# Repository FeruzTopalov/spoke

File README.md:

# **SPOKE*** - _Stay close!_ 
_*Like a spoke in a wheel_

<p align="center">
🔓 Open-source<br>
🛠️ Open-hardware<br>
🛰️ GPS-based<br>
📡 LoRa-enabled<br>
🔋 Off-grid<br>
✨ Feature-rich<br>
🧭 Local Relative Navigation System<br>
<br>
or<br>
<br>
📍 just a LoRa GPS tracker for group 😉<br>
</p>

---

## 📋 Table of Contents

- [About](#about)
- [Use Cases](#use-cases)
- [Key Features](#key-features)
- [Hardware](#hardware)
- [Technology & How It Works](#technology--how-it-works)
- [Navigation Algorithms](#navigation-algorithms)
- [Getting Started](#getting-started)
- [Configuration](#configuration)
- [Frequency Bands](#frequency-bands)
- [Community](#community)
- [Contributing](#contributing)
- [Support the Project](#support-the-project)

---

## About

**Spoke** is a GPS tracker for a group of up to 5 members. It enables **real-time positional data sharing** in a group, providing **Distance** and **Azimuth** information in a **radar-like interface** where a 360-degree azimuth circle shows your direction as a **spoke** and azimuth to target as a **notch**. 

Besides navigation function, Spoke has **extra safety features** like: 
- **Alarm distress signal** - with a dedicated red button to easily call group members for help
- **Timeout alert** - with configurable timeout in seconds
- **Radial geo-fence alert** - with configurable distance in meters

---

## Use Cases

Spoke's open-source nature and flexible hardware make it adaptable to numerous scenarios:

- 🥾 **Hiking & Trekking** - Keep your group together on trails
- 🧗 **Climbing & Mountaineering** - Track team members on challenging terrain
- ⛵ **Sailing & Boating** - Monitor vessel positions without AIS
- 🎿 **Skiing & Snowboarding** - Stay connected in backcountry areas
- 🏕️ **Camping & Outdoor Adventures** - Know where everyone is at camp
- 🐕 **Hunting with Dogs** - Track your hunting dogs' positions
- 📦 **Asset Tracking** - Monitor equipment or vehicles in remote locations
- 🚴 **Off-road Biking** - Keep your riding group coordinated
- 🔍 **Search & Rescue** - Coordinate team members during operations

---

## Key Features

### Navigation & Tracking
- **Real-time group tracking** for up to 5 devices with radar-like display
- **Absolute positioning** with GPS coordinates (latitude, longitude, altitude)
- **Relative positioning** with distance and azimuth to each group member
- **Memory points** to save locations and navigate to them later
- **Interactive eCompass** for quick orientation with ad-hoc calibration support
- **Magnetic and True North** display modes

### Communication
- **LoRa long-range radio** communication (up to several kilometers)
- **TDMA synchronization** using GPS PPS signal for collision-free transmission
- **Multi-band support:** 433 MHz or 868 MHz with 1% duty cycle compliance
- **License-free frequency channels** depending on the frequency band and country of operation
- **Configurable update intervals:** 10, 30, 60, or 120 seconds

### Safety Features
- **GeoFence alert** - notification when a member leaves defined circle around you
- **Timeout alert** - notification when connection to a member is lost for a defined time
- **Dedicated alarm button** for emergency signaling
- **Battery-low monitoring** and notification to other members

---

## Hardware

### PCB

Spoke is assembled on a simple, 2-layer, 1.6 mm thick PCB of 100 x 50 mm size. It uses well-known and popular electronic components that are easy to get. Some of them may be or already are obsolete, but are still available on the market, or even in your own stock! Spoke is not critical to values and nominals of components, so it can be easily adapted to your parts source. Some components are optional to install, which adds extra flexibility if you do not need particular functionality.

### Core Components

| Component | Specification | Purpose | Install option |
|-----------|---------------|---------|---------|
| **MCU** | STM32F103C8T6 (BluePill) | Main processing unit | Mandatory |
| **GPS Module** | QUESCAN models G10A-F30 or TU10-F <br> or any other with wires | Position and time synchronization | Mandatory |
| **Radio Module** | Semtech SX126x-based <br> E22-400M22S or E22-900M22S | LoRa communication | Mandatory |
| **Display** | 1.3" Monochrome LCD (ST7567 controller) | User interface | Mandatory |
| **eCompass** | LSM303DLHC | Orientation and motion sensing | Optional |
| **USB Interface** | Type-C with CP2102N-28 USB-UART converter | Programming and Nav data stream | Optional |
| **BLE Module** | E104-BT5005A BLE-UART bridge | Wireless Nav data stream | Optional |
| **Multiplexer** | 74HC4052PW | Switching Nav data stream between USB and BLE | Optional |
| **Power Regulator** | LM3671MF-3.3 DC/DC | Efficient power management |Mandatory |
| **Battery** | Li-ion/Li-Po 2200 mAh <br> 70 x 40 x 6 mm max  | Power source | Mandatory |
| **Charging IC** | TP4056 | Battery charging management | Mandatory |

---

## Technology & How It Works

### Software Architecture

Spoke firmware is written in **pure C** using CMSIS and runs on the STM32F103C8T6 ARM Cortex-M3 microcontroller. The firmware features:

- **Modular design** with compile-time configuration
- **Watchdog protection** for system stability
- **Peripheral clock gating** for power optimization
- **DMA-based data processing** for efficiency
- **Double-precision calculations** for navigation accuracy

### GPS Processing

- **Configurable baud rates** (9600, 38400, 57600 and 115200 baud)
- **NMEA-0183 stream parsing** with essential navigation sentences (RMC, GGA, GSA, GSV)
- **PPS (Pulse Per Second)** signal for precise time synchronization
- **Data extracted:** Time, date, position (lat/lon/alt), speed, course over ground, satellites info, PDOP quality

### Communication Protocol

Spoke uses **Time Division Multiple Access (TDMA)** synchronized by GPS PPS signal:

1. **Time Reference:** GPS PPS signal triggers 900 ms processing window
2. **Data Collection:** NMEA data parsed and position prepared in the 900 ms window
3. **Time Slots:** Each device (numbered 1 to 5) transmits on dedicated even second of time: x0, x2, x4, x6, x8; where x = 0...5 depends on update interval setting
4. **Collision Avoidance:** TDMA ensures devices do not interfere with each other
5. **Update Intervals:** Configurable at 10, 30, 60, or 120 seconds

### LoRa Configuration

**Modulation Parameters:**
- **Spreading Factor:** SF12
- **Bandwidth:** 125 kHz
- **Coding Rate:** 4/8
- **Header:** Explicit mode, header disabled
- **CRC:** Enabled
- **Output Power:** -9 to +22 dBm (configurable)

**Packet Structure (13 bytes payload):**

| Preamble | Payload | CRC |
|----------|---------|-----|
| 8 symbols | 13 bytes | 2 bytes |

**Payload Format:**

| Flags | Device Number | Device ID | Latitude | Longitude | Altitude |
|--------------------|-------|----------|-----------|----------|----------|
| 1 byte | 1 byte | 1 byte | 4 bytes | 4 bytes | 2 bytes |

**Time on Air:** 1.188 seconds per packet

### Nav data Output

Complete navigational data of all devices and saved points is available via:
- **Physical UART:** 115200 baud, accessible at console pin header
- **USB-UART:** Wired through CP2102N converter
- **BLE-UART:** Wireless via E104-BT5005A module
- **Format:** ISO 8601 timestamp + Base64-encoded Nav data

### Nav data Format

- **ISO 8601 Timestamp:** YYYY-MM-DDTHH:MM:SS+hh:mm where +/-hh:mm is timezone configured by user
  - 25 bytes size, fixed
- **Base64 Nav data:**
  - 9 navigation objects max (5 devices and 4 saved points)
  - 19 bytes each object
  - 171 bytes max Nav data size (raw, before Base64 encoding)
  - 228 bytes max Nav data size (final, after Base64 encoding)
  - **Format:** (little-endian)
    - Device Number - 1 byte, unsigned, range from 1 to 9
    - Device ID - 1 byte, ASCII char
    - Internal flags - 1 byte, bit field
      - bit 0 - is nav object your device
      - bit 1 - is nav object a memory point
      - bit 2 - is fence alarm triggered
      - bit 3 - is timeout alarm triggered
      - bit 4 - is nav object online (i.e. successful communication at last time slot)
    - External flags - 1 byte, bit field
      - bit 0 - is nav object in alarm
      - bit 1 - is nav object a beacon
      - bit 2 - is nav object in low battery state
      - bit 3 - is nav object's motion detected
      - bit 4 - is nav object's PDOP good
    - SNR value - 1 byte, signed (actual for devices only, but kept as 0 for saved points for unification)
    - Timeout  - 4 bytes, unsigned, seconds since last activity
    - Latitude - 4 bytes, float, decimal degree
    - Longitude - 4 bytes, float, decimal degree
    - Altitude - 2 bytes, signed, meters above mean sea level
- **Example:** "2025-03-02T10:45:00+02:00 AUERGAAAAAB+WUNCvHUSQGQA\r\n"
  - Max total size: 25 + 1 (space) + 228 + 2 (cr & lf) = 256 bytes

---

## Navigation Algorithms

Spoke implements high-precision navigation calculations using established mathematical formulas:

### Distance Calculation - Haversine Formula

The [Haversine formula](https://en.wikipedia.org/wiki/Haversine_formula) calculates the great-circle distance between two points on a sphere:

- **Advantages:** Numerically well-conditioned for small distances
- **Implementation:** Double-precision floating-point for accuracy
- **Accuracy:** <1% error for distances up to 300 km

### Bearing Calculation - Loxodrome (Rhumb Line)

The [Loxodrome formula](https://en.wikipedia.org/wiki/Rhumb_line) determines constant bearing to destination:

- **Advantages:** Provides constant compass bearing (easier to follow)
- **Implementation:** Accounts for Mercator projection
- **Practical Use:** More useful than great-circle route for navigation
- **Accuracy:** Very close in distance to Great Circle Route at short distances

<p align="center">
  <i>(Mercator projection - courtesy of <a href="https://www.esri.com/arcgis-blog/products/product/mapping/mercators-500th-birthday/">ESRI</a>)</i>
</p>

---

## Getting Started

### Prerequisites

**Hardware Requirements:**
- Spoke devices (at least two to form a group)
- USB Type-C cable for UART bootloader programming
- ST-Link for SWD programming
- Lithium-ion battery
- LoRa antenna (433 MHz or 868 MHz, depending on configuration)

**Software Requirements:**
- STM32CubeIDE for compilation
- STM32CubeProgrammer for flashing

### HW & FW Versions

To access a specific version of Spoke HW or FW refer to Git Tags. See the latest versions in [CHANGELOG](CHANGELOG.md)

### Building Firmware

See [Configuration, Compilation and Programming Instruction](CubeIDE/README.md)

---

## Configuration

### Compile-Time Configuration (config.h)

The firmware uses compile-time defines for hardware-specific settings:

```c
/* PART A - user-defined */

/* Step 1 - Select Spoke HW Revision */
//#define SPOKE_HW_REV_1_x	/* Spoke HW 1.x */
//#define SPOKE_HW_REV_2_0	/* Spoke HW 2.0 */
#define SPOKE_HW_REV_2_1	/* Spoke HW 2.1 */

/* Step 2 - Select GPS Baud Speed */
//#define GPS_BAUD_9600
#define GPS_BAUD_38400
//#define GPS_BAUD_57600
//#define GPS_BAUD_115200	/* Operation at 115200 is not guaranteed due to limited buffer size */

/* Step 3 - Select Frequency Band */
//#define FREQ_BAND_433		/* Define for E22-400M22S module (SX1268) if it is populated in any HW revision */
#define FREQ_BAND_868		/* Define for E22-900M22S module (SX1262) if it is populated in any HW revision */
```

### Runtime Configuration (Settings Menu)

Access settings via button interface:
- **Device number** (1 - 5)
- **Group size** (2 - 5)
- **Device ID** (A - Z)
- **Update interval** (10, 30, 60, 120 sec)
- **Frequency channel** (1 - 8 for 433 band, 1 - 21 for 868 band)
- **TX power** (-9, 0, +10, +14, +22 dBm)
- **Timeout alarm** (0 - 3600 sec, 10 sec increment) 
- **Fence** (0 - 5000 m, 10 m increment)
- **Timezone** (-12 - +14 h, 15 min increment)

---

## Frequency Bands

⚠️ **Important:** Ensure you comply with your local radio frequency regulations before operating Spoke! Configure update interval, frequency channel and TX output power according to them!

### 433 MHz Band

| Channel | Frequency |
|---------|-----------|
| CH 1 | 433.175 |
| CH 2 | 433.375 |
| CH 3 | 433.575 |
| CH 4 | 433.775 |
| CH 5 | 433.975 |
| CH 6 | 434.175 |
| CH 7 | 434.375 |
| CH 8 | 434.575 |

### 868 MHz Band

| Channel | Frequency |
|---------|-----------|
| CH 1  | 865.100 |
| CH 2  | 865.300 |
| CH 3  | 865.500 |
| CH 4  | 865.700 |
| CH 5  | 865.900 |
| CH 6  | 866.100 |
| CH 7  | 866.300 |
| CH 8  | 866.500 |
| CH 9  | 866.700 |
| CH 10 | 866.900 |
| CH 11 | 867.100 |
| CH 12 | 867.300 |
| CH 13 | 867.500 |
| CH 14 | 867.700 |
| CH 15 | 867.900 |
| CH 16 | 868.100 |
| CH 17 | 868.300 | 
| CH 18 | 868.500 |
| CH 19 | 868.700 |
| CH 20 | 868.900 |
| CH 21 | 869.100 |

---

## Community

- **Telegram Group: [RU, EN]** [https://t.me/lrns_eleph](https://t.me/lrns_eleph)
  - Share experiences and demonstrations
  - Get help with building and troubleshooting
  - Discuss new features and improvements
  - Connect with other Spoke users

---

## Contributing

We welcome contributions from the community! Here is how you can help:

1. **Test and Report Issues**
   - Build the device and test in real-world conditions
   - Report bugs via GitHub Issues
   - Share your use case and feedback

2. **Code Contributions**
   - Fork the repository
   - Create a feature branch
   - Submit pull requests with improvements
   - Follow existing code style and conventions

3. **Hardware Improvements**
   - Suggest PCB layout optimizations
   - Test alternative components
   - Share manufacturing tips

4. **Documentation**
   - Improve README and guides
   - Add translations
   - Create tutorials and examples

5. **Community Support**
   - Help other users in Telegram group
   - Share your builds and experiences
   - Write blog posts or make videos about Spoke

---

## Support the Project

The best way to support Spoke is through **active participation**:
- Build and test the device
- Report issues and contribute fixes
- Join the community and help others
- Share your experience and use cases

### Financial Support
If you'd like to support development financially:
- **Boosty:** [https://boosty.to/feruztopalov/donate](https://boosty.to/feruztopalov/donate)
  - One-time donations
  - Subscriptions with exclusive bonuses

---

<p align="center">
  Made with ❤️ by the Spoke community
</p>

<p align="center">
  <strong>Stay Connected. Stay Safe. Stay Close.</strong>
</p>

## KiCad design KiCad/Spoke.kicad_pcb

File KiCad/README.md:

# Hardware design

Designed in KiCad version 9.0.4  
PCB stack-up: 100 x 50 mm, typical FR-4, 2 layers, 1 o.z., 1.6 mm thickness, 0.2 mm track/clearance, 0.3/0.6 mm via

See PRODUCTION folder for:
- "3D" - STEP model of PCB
- "BOM" - Bill of Materials
- "PCB" - Gerber files
- "SCH" - Circuit schematic

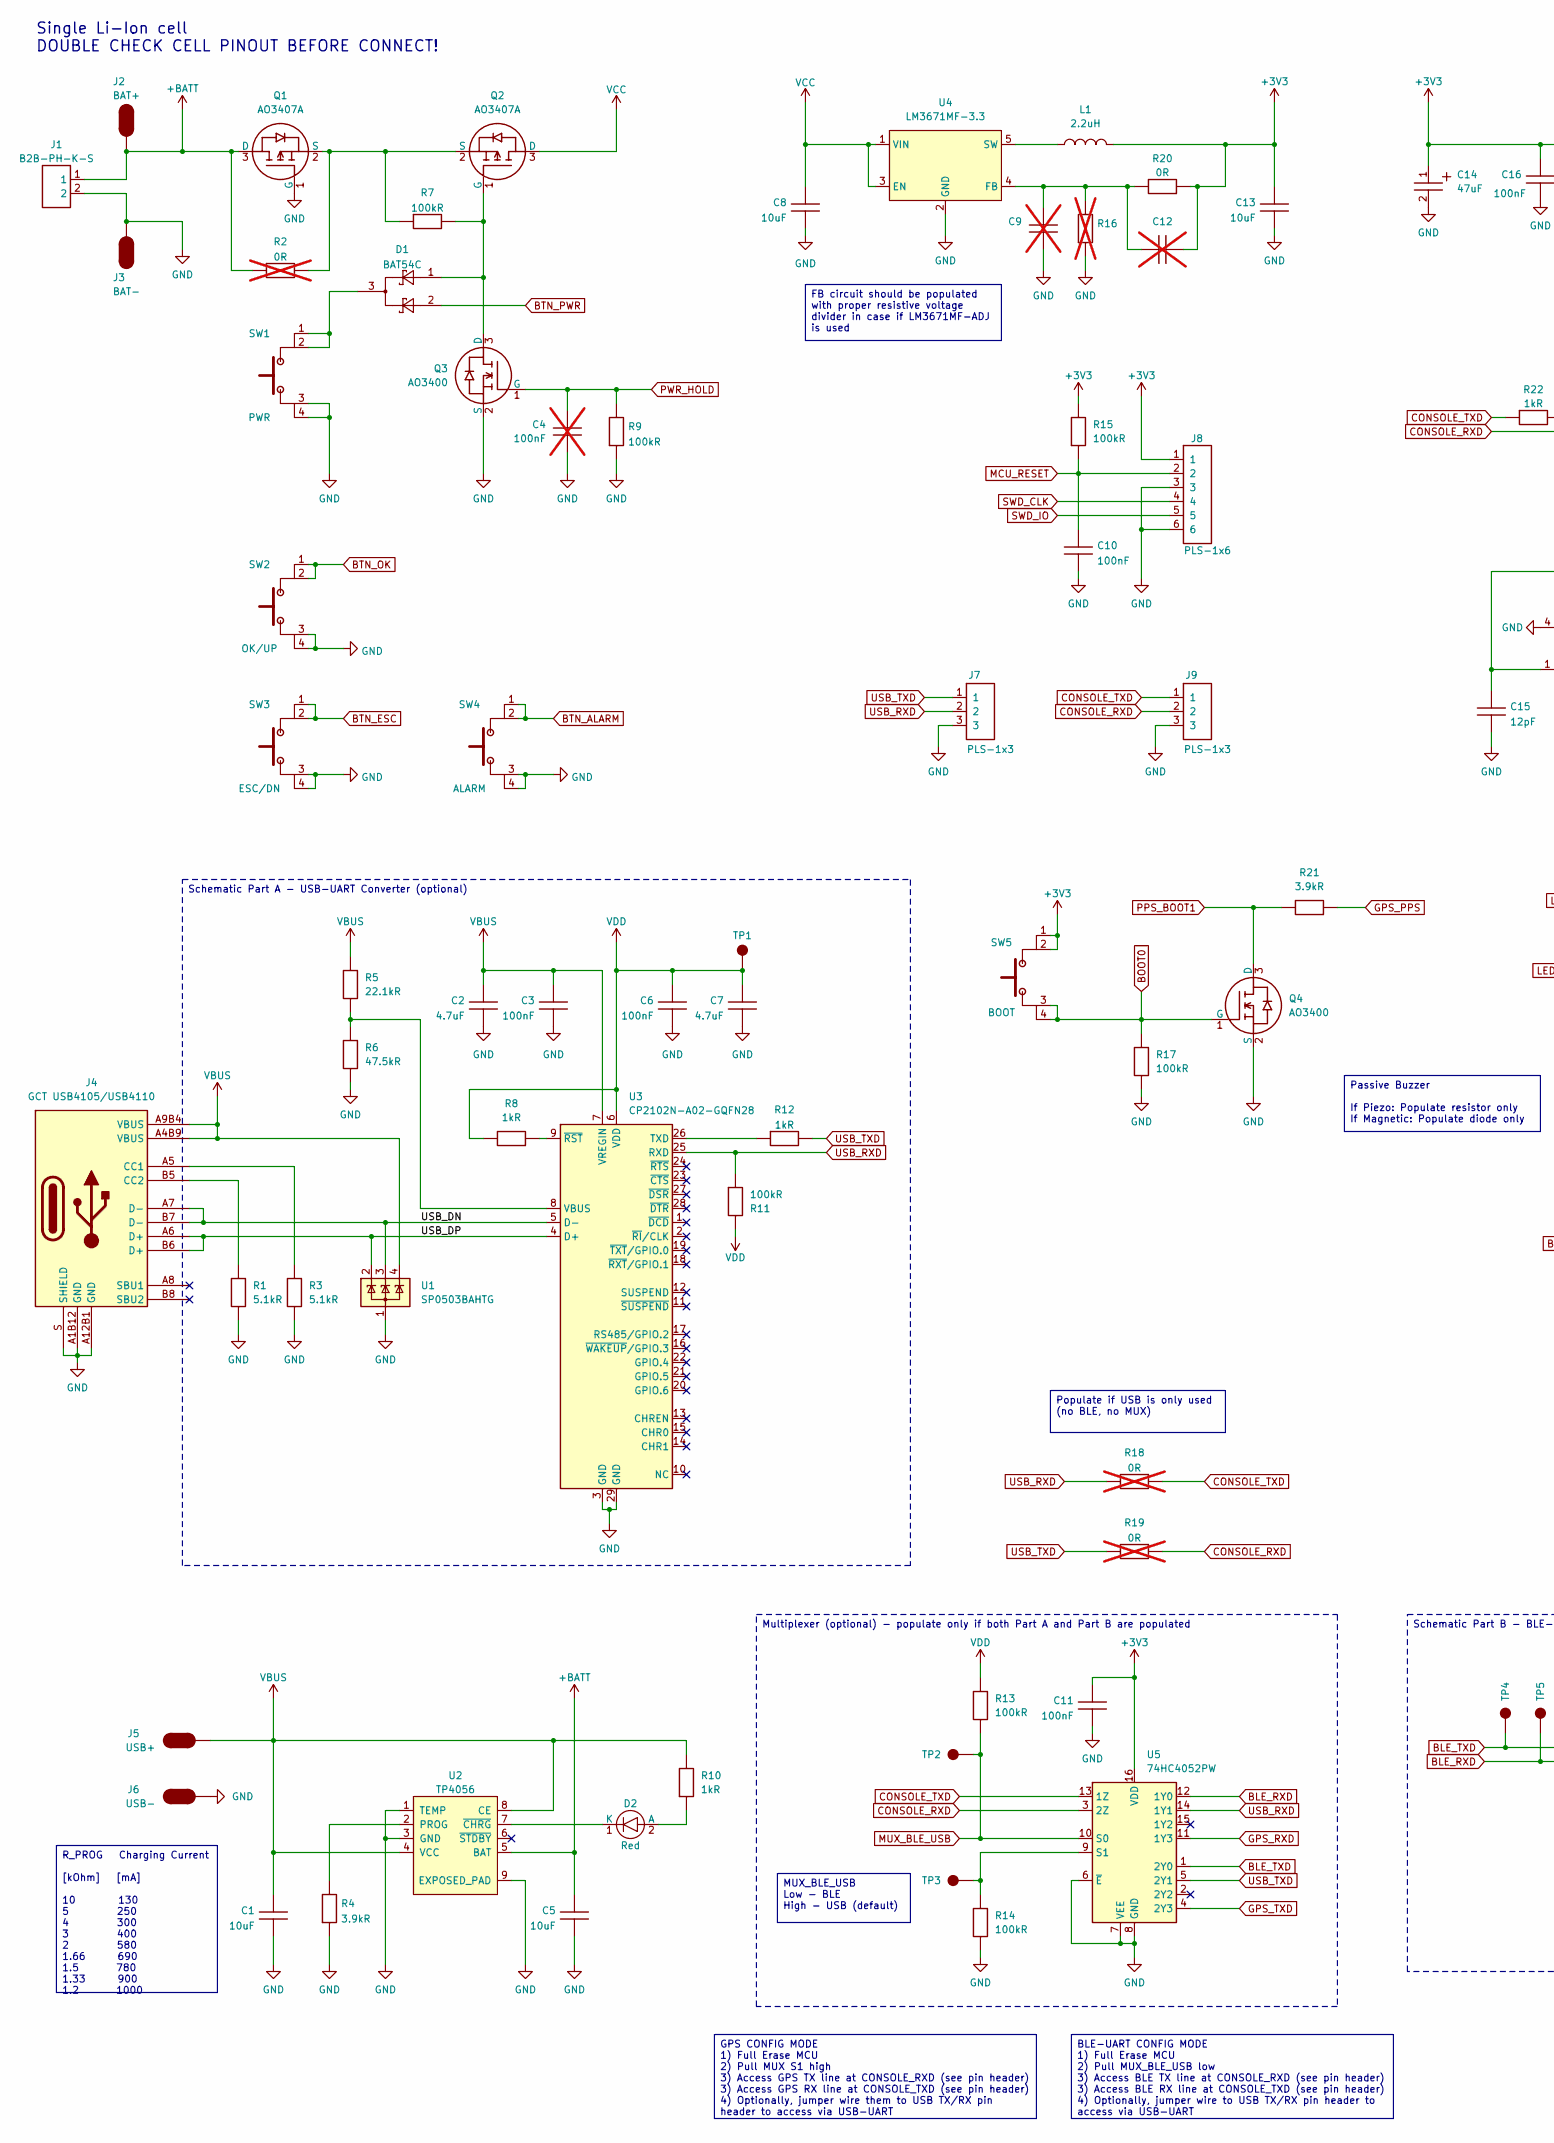
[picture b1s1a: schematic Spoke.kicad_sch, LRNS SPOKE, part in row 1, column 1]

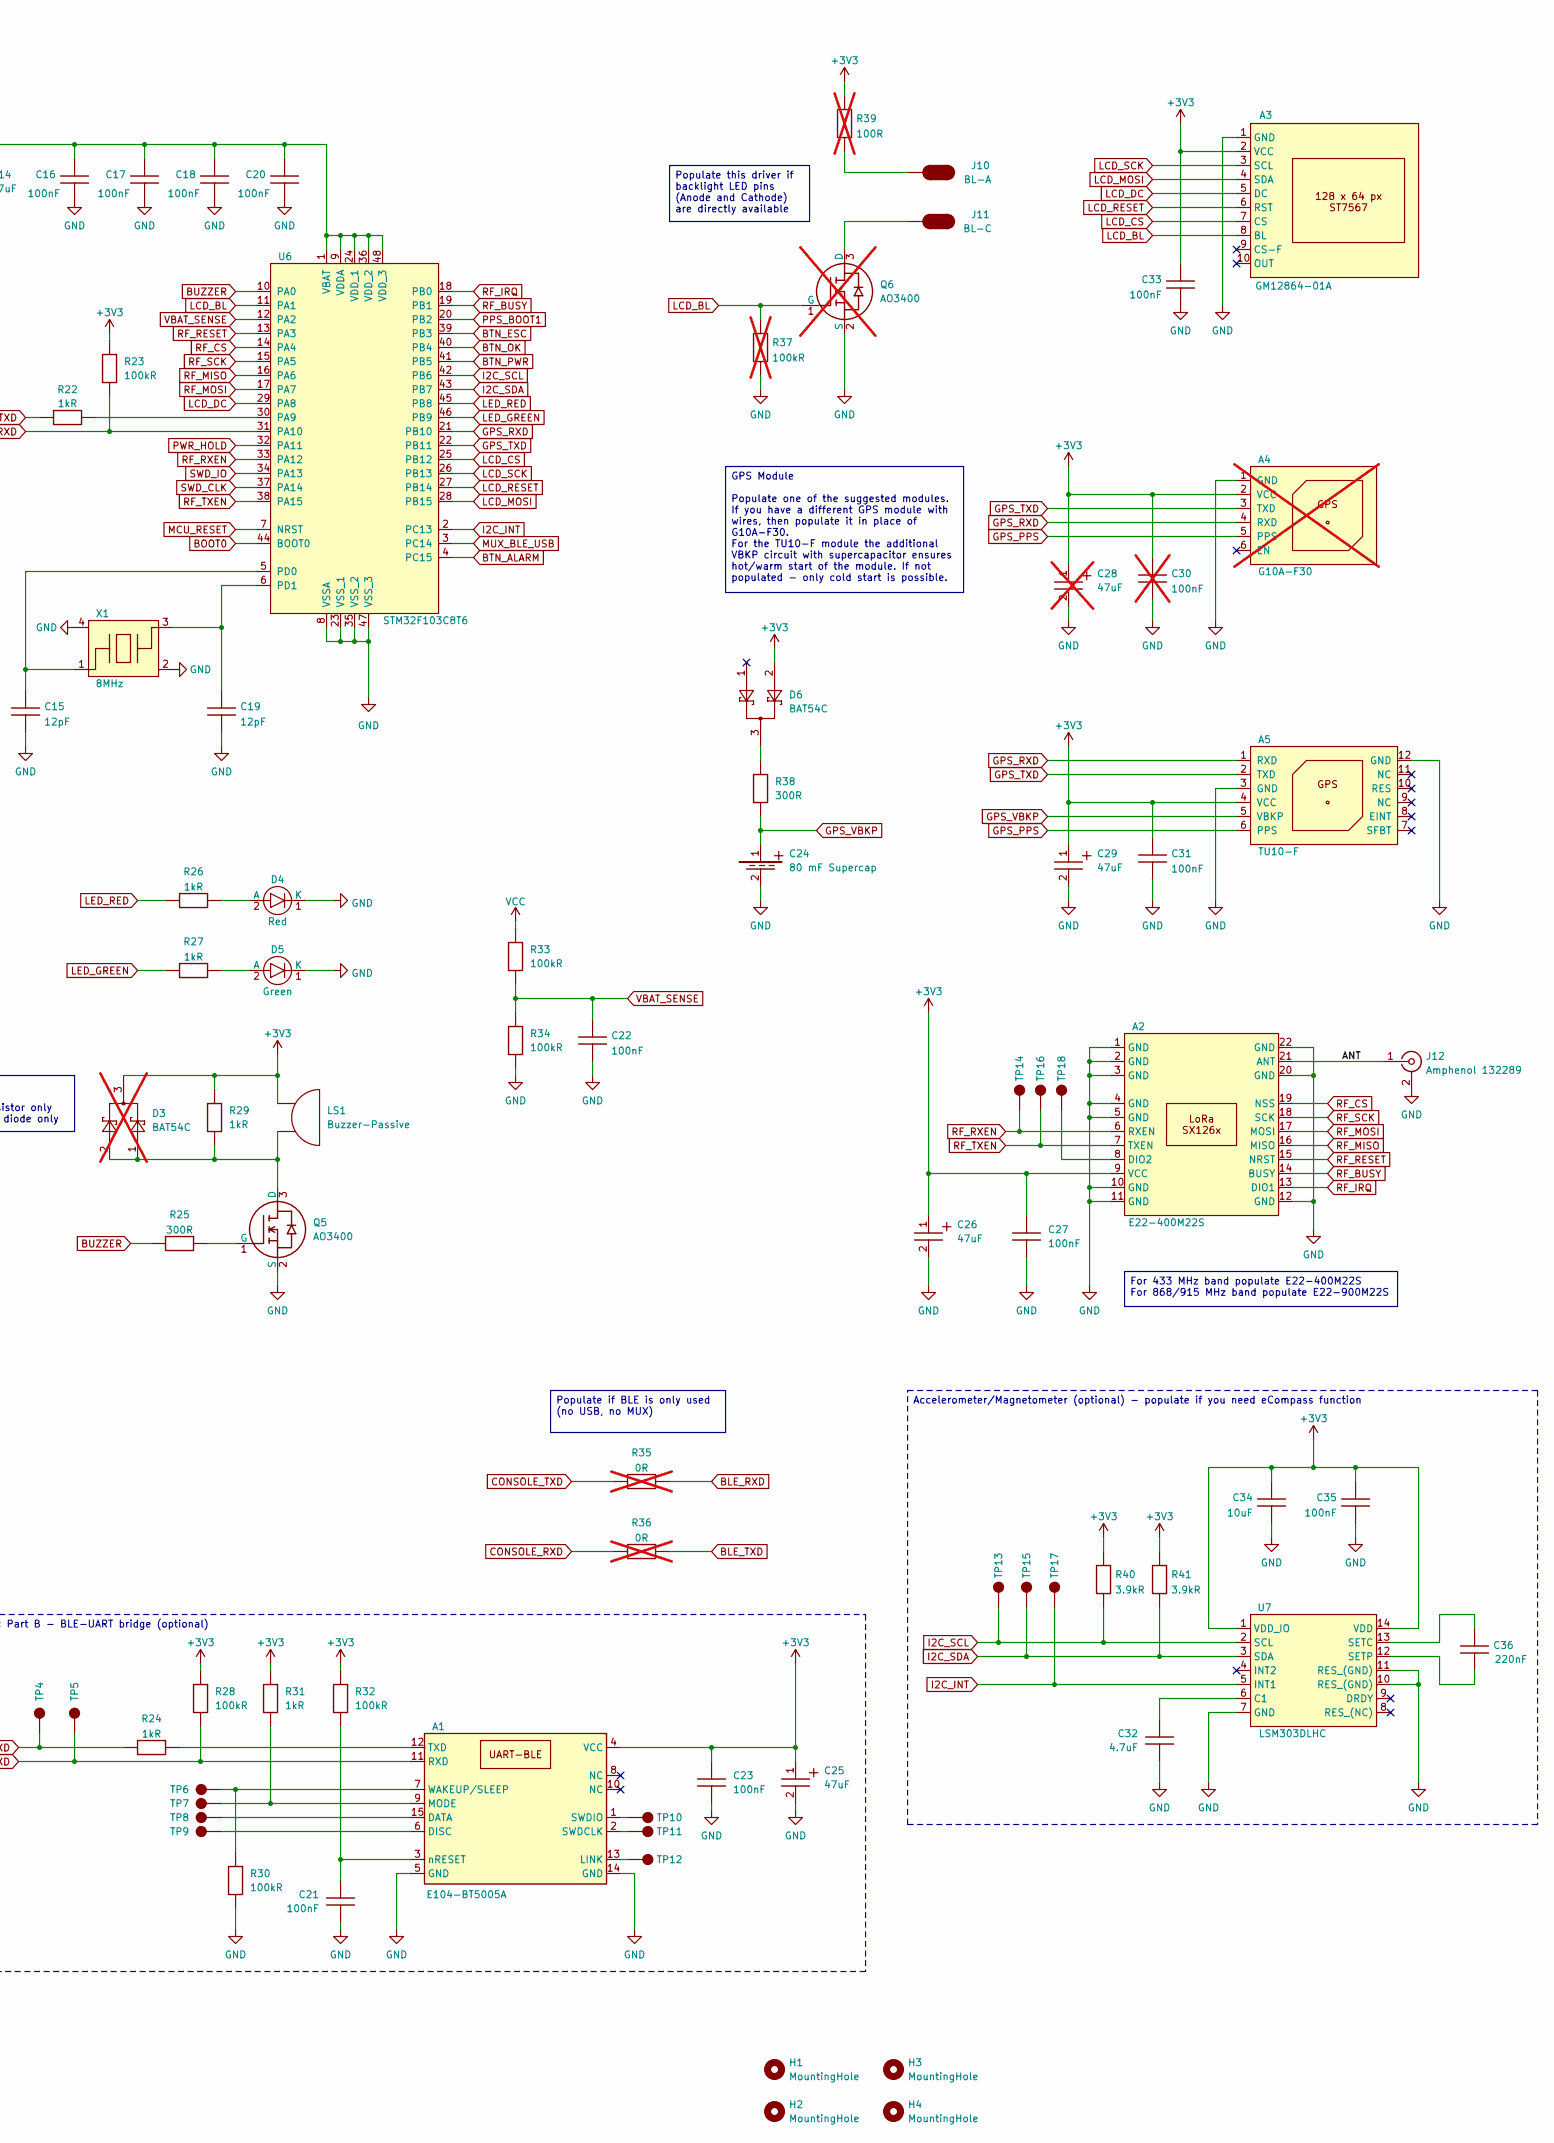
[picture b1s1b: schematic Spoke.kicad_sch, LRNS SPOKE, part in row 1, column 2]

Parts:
A1: E104-BT5005A
A2: E22-400M22S; E22
A3: GM12864-01A
A4: G10A-F30; not fitted
A5: TU10-F
C1, C5, C8, C13, C34: 10uF; C1206
C2, C7, C32: 4.7uF; C0805
C3, C6, C10, C11, C16, C17, C18, C20, C21, C22, C23, C27, C31, C33, C35: 100nF; C0603
C4, C30: 100nF; C0603; not fitted
C9, C12: C0603; not fitted
C14, C25, C26, C29: 47uF; C_tantA
C15, C19: 12pF; C0603
C24: 80 mF Supercap; XH414HG-IV01E
C28: 47uF; C_tantA; not fitted
C36: 220nF; C0603
D1, D6: BAT54C; SOT-23
D2, D4: Red; LED_3mm
D3: BAT54C; SOT-23; not fitted
D5: Green; LED_3mm
H1, H2, H3, H4: MountingHole; MountingHole_3.2mm_M3
J1: B2B-PH-K-S; B2B-PH-2.0
J2: BAT+; Pad_oval
J3: BAT-; Pad_oval
J4: GCT USB4105/USB4110; USB_C_16p_GCT4105
J5: USB+; Pad_oval
J6: USB-; Pad_oval
J7, J9: PLS-1x3; Header_1x3
J8: PLS-1x6; Header_1x6
J10: BL-A; Pad_oval
J11: BL-C; Pad_oval
J12: Amphenol 132289; SMA
L1: 2.2uH; L1616
LS1: Buzzer-Passive; Buzzer
Q1, Q2: AO3407A; SOT-23
Q3, Q4, Q5: AO3400; SOT-23
Q6: AO3400; SOT-23; not fitted
R1, R3: 5.1kR; R0603
R2, R18, R19, R35, R36: 0R; R0603; not fitted
R4, R21, R40, R41: 3.9kR; R0603
R5: 22.1kR; R0603
R6: 47.5kR; R0603
R7, R9, R11, R13, R14, R15, R17, R23, R28, R30, R32, R33, R34: 100kR; R0603
R8, R10, R12, R22, R24, R26, R27, R29, R31: 1kR; R0603
R16: R0603; not fitted
R20: 0R; R0603
R25, R38: 300R; R0603
R37: 100kR; R0603; not fitted
R39: 100R; R1206; not fitted
SW1, SW2, SW3, SW4, SW5: Button_6x6
TP1, TP2, TP3, TP4, TP5, TP6, TP7, TP8, TP9, TP10, TP11, TP12, TP13, TP14, TP15, TP16, TP17, TP18: Pad-Round; Pad_round
U1: SP0503BAHTG; SOT-143
U2: TP4056; SOIC-8-EP
U3: CP2102N-A02-GQFN28; QFN-28
U4: LM3671MF-3.3; SOT-23-5
U5: 74HC4052PW; TSSOP-16
U6: STM32F103C8T6; LQFP-48
U7: LSM303DLHC; LGA-14
X1: 8MHz; Xtal_3225

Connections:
+3V3: A1.4 (VCC), A2.9 (VCC), A3.2 (VCC), A4.2 (VCC), A5.4 (VCC), C11.1, C12.2, C13.2, C14.1, C16.1, C17.1, C18.1, C20.1, C23.1, C25.1, C26.1, C27.1, C28.1, C29.1, C30.1, C31.1, C33.1, C34.2, C35.1, D3.3, D6.2, J8.1, L1.2, LS1.1, R15.2, R20.1, R23.2, R28.1, R29.2, R31.1, R32.1, R39.2, R40.2, R41.2, SW5.1, SW5.2, U5.16 (VDD), U6.1 (VBAT), U6.9 (VDDA), U6.24 (VDD_1), U6.36 (VDD_2), U6.48 (VDD_3), U7.1 (VDD_IO), U7.14 (VDD)
+BATT: C5.2, J1.1, J2.1, Q1.3 (D), R2.1, U2.5 (BAT)
/ANT: A2.21 (ANT), J12.1 (RF)
/USB_DN: J4.A7 (D-), J4.B7 (D-), U1.3 (K), U3.5 (D-)
/USB_DP: J4.A6 (D+), J4.B6 (D+), U1.2 (K), U3.4 (D+)
BLE_RXD: A1.11 (RXD), R28.2, R35.2, TP5.1, U5.12 (1Y0)
BLE_TXD: R24.1, R36.2, TP4.1, U5.1 (2Y0)
BOOT0: Q4.1 (G), R17.1, SW5.3 (2), SW5.4 (2), U6.44 (BOOT0)
BTN_ALARM: SW4.1, SW4.2, U6.4 (PC15)
BTN_ESC: SW3.1, SW3.2, U6.39 (PB3)
BTN_OK: SW2.1, SW2.2, U6.40 (PB4)
BTN_PWR: D1.2, U6.41 (PB5)
BUZZER: R25.1, U6.10 (PA0)
CONSOLE_RXD: J9.2, R19.1, R23.1, R36.1, U5.3 (2Z), U6.31 (PA10)
CONSOLE_TXD: J9.1, R18.1, R22.1, R35.1, U5.13 (1Z)
GND: A1.5 (GND), A1.14 (GND), A2.1 (GND), A2.2 (GND), A2.3 (GND), A2.4 (GND), A2.5 (GND), A2.10 (GND), A2.11 (GND), A2.12 (GND), A2.20 (GND), A2.22 (GND), A3.1 (GND), A4.1 (GND), A5.3 (GND), A5.12 (GND), C1.1, C2.1, C3.1, C4.2, C5.1, C6.1, C7.1, C8.1, C9.2, C10.2, C11.2, C13.1, C14.2, C15.2, C16.2, C17.2, C18.2, C19.2, C20.2, C21.2, C22.2, C23.2, C24.2, C25.2, C26.2, C27.2, C28.2, C29.2, C30.2, C31.2, C32.1, C33.2, C34.1, C35.2, D4.1 (K), D5.1 (K), J1.2, J3.1, J4.A1B12 (GND), J4.A12B1 (GND), J4.S (SHIELD), J6.1, J7.3, J8.3, J8.6, J9.3, J12.2 (GND), Q1.1 (G), Q3.2 (S), Q4.2 (S), Q5.2 (S), Q6.2 (S), R1.2, R3.2, R4.1, R6.2, R9.1, R14.2, R16.1, R17.2, R30.2, R34.1, R37.1, SW1.3 (2)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
GPS_PPS: A4.5 (PPS), A5.6 (PPS), R21.1
GPS_RXD: A4.4 (RXD), A5.1 (RXD), U5.11 (1Y3), U6.21 (PB10)
GPS_TXD: A4.3 (TXD), A5.2 (TXD), U5.4 (2Y3), U6.22 (PB11)
GPS_VBKP: A5.5 (VBKP), C24.1, R38.1
I2C_INT: TP17.1, U6.2 (PC13), U7.5 (INT1)
I2C_SCL: R40.1, TP13.1, U6.42 (PB6), U7.2 (SCL)
I2C_SDA: R41.1, TP15.1, U6.43 (PB7), U7.3 (SDA)
LCD_BL: A3.8 (BL), Q6.1 (G), R37.2, U6.11 (PA1)
LCD_CS: A3.7 (CS), U6.25 (PB12)
LCD_DC: A3.5 (DC), U6.29 (PA8)
LCD_MOSI: A3.4 (SDA), U6.28 (PB15)
LCD_RESET: A3.6 (RST), U6.27 (PB14)
LCD_SCK: A3.3 (SCL), U6.26 (PB13)
LED_GREEN: R27.1, U6.46 (PB9)
LED_RED: R26.1, U6.45 (PB8)
MCU_RESET: C10.1, J8.2, R15.1, U6.7 (NRST)
MUX_BLE_USB: R13.2, TP2.1, U5.10 (S0), U6.3 (PC14)
unnamed: A1.15 (DATA), TP8.1
unnamed: A1.6 (DISC), TP9.1
unnamed: A1.13 (LINK), TP12.1
unnamed: A1.9 (MODE), R31.2, TP7.1
unnamed: A1.2 (SWDCLK), TP11.1
unnamed: A1.1 (SWDIO), TP10.1
unnamed: A1.12 (TXD), R24.2
unnamed: A1.7 (WAKEUP/SLEEP), R30.1, TP6.1
unnamed: A1.3 (nRESET), C21.1, R32.2
unnamed: A2.8 (DIO2), TP18.1
unnamed: D1.3, SW1.1, SW1.2
unnamed: D2.2 (A), R10.1
unnamed: D2.1 (K), U2.7 (~CHRG)
unnamed: D4.2 (A), R26.2
unnamed: D5.2 (A), R27.2
unnamed: D6.3, R38.2
unnamed: J4.A5 (CC1), R3.1
unnamed: J4.B5 (CC2), R1.1
unnamed: J10.1, R39.1
unnamed: Q1.2 (S), Q2.2 (S), R2.2, R7.1
unnamed: D1.1, Q2.1 (G), Q3.3 (D), R7.2
unnamed: D3.1, D3.2, LS1.2, Q5.3 (D), R29.1
unnamed: Q5.1 (G), R25.2
unnamed: J11.1, Q6.3 (D)
unnamed: R4.2, U2.2 (PROG)
unnamed: R12.1, U3.26 (TXD)
unnamed: R5.2, R6.1, U3.8 (VBUS)
unnamed: R8.1, U3.9 (~RST)
unnamed: C9.1, C12.1, R16.2, R20.2, U4.4 (FB)
unnamed: L1.1, U4.5 (SW)
unnamed: R14.1, TP3.1, U5.9 (S1)
unnamed: R22.2, U6.30 (PA9)
unnamed: C15.1, U6.5 (PD0), X1.1
unnamed: C19.1, U6.6 (PD1), X1.3
unnamed: C32.2, U7.6 (C1)
unnamed: C36.1, U7.13 (SETC)
unnamed: C36.2, U7.12 (SETP)
PPS_BOOT1: Q4.3 (D), R21.2, U6.20 (PB2)
PWR_HOLD: C4.1, Q3.1 (G), R9.2, U6.32 (PA11)
RF_BUSY: A2.14 (BUSY), U6.19 (PB1)
RF_CS: A2.19 (NSS), U6.14 (PA4)
RF_IRQ: A2.13 (DIO1), U6.18 (PB0)
RF_MISO: A2.16 (MISO), U6.16 (PA6)
RF_MOSI: A2.17 (MOSI), U6.17 (PA7)
RF_RESET: A2.15 (NRST), U6.13 (PA3)
RF_RXEN: A2.6 (RXEN), TP14.1, U6.33 (PA12)
RF_SCK: A2.18 (SCK), U6.15 (PA5)
RF_TXEN: A2.7 (TXEN), TP16.1, U6.38 (PA15)
SWD_CLK: J8.4, U6.37 (PA14)
SWD_IO: J8.5, U6.34 (PA13)
USB_RXD: J7.2, R11.1, R18.2, U3.25 (RXD), U5.14 (1Y1)
USB_TXD: J7.1, R12.2, R19.2, U5.5 (2Y1)
VBAT_SENSE: C22.1, R33.1, R34.2, U6.12 (PA2)
VBUS: C1.2, C2.2, C3.2, J4.A4B9 (VBUS), J4.A9B4 (VBUS), J5.1, R5.1, R10.2, U1.4 (K), U2.4 (VCC), U2.8 (CE), U3.7 (VREGIN)
VCC: C8.2, Q2.3 (D), R33.2, U4.1 (VIN), U4.3 (EN)
VDD: C6.2, C7.2, R8.2, R11.2, R13.1, TP1.1, U3.6 (VDD)

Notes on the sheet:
Single Li-Ion cell DOUBLE CHECK CELL PINOUT BEFORE CONNECT!
Passive Buzzer If Piezo: Populate resistor only If Magnetic: Populate diode only
FB circuit should be populated with proper resistive voltage divider in case if LM3671MF-ADJ is used
GPS Module Populate one of the suggested modules. If you have a different GPS module with wires, then populate it in place of G10A-F30. For the TU10-F module the additional VBKP circuit with supercapacitor ensures hot/warm start of the module. If not populated - only cold start is possible.
GPS CONFIG MODE 1) Full Erase MCU 2) Pull MUX S1 high 3) Access GPS TX line at CONSOLE_RXD (see pin header) 3) Access GPS RX line at CONSOLE_TXD (see pin header) 4) Optionally, jumper wire them to USB TX/RX pin header to access via USB-UART
Schematic Part B - BLE-UART bridge (optional)
Populate if BLE is only used (no USB, no MUX)
R_PROG Charging Current [kOhm] [mA] 10 130 5 250 4 300 3 400 2 580 1.66 690 1.5 780 1.33 900 1.2 1000
MUX_BLE_USB Low - BLE High - USB (default)
Populate if USB is only used (no BLE, no MUX)
Schematic Part A - USB-UART Converter (optional)
BLE-UART CONFIG MODE 1) Full Erase MCU 2) Pull MUX_BLE_USB low 3) Access BLE TX line at CONSOLE_RXD (see pin header) 3) Access BLE RX line at CONSOLE_TXD (see pin header) 4) Optionally, jumper wire to USB TX/RX pin header to access via USB-UART
Populate this driver if backlight LED pins (Anode and Cathode) are directly available
Accelerometer/Magnetometer (optional) - populate if you need eCompass function
Multiplexer (optional) - populate only if both Part A and Part B are populated
For 433 MHz band populate E22-400M22S For 868/915 MHz band populate E22-900M22S

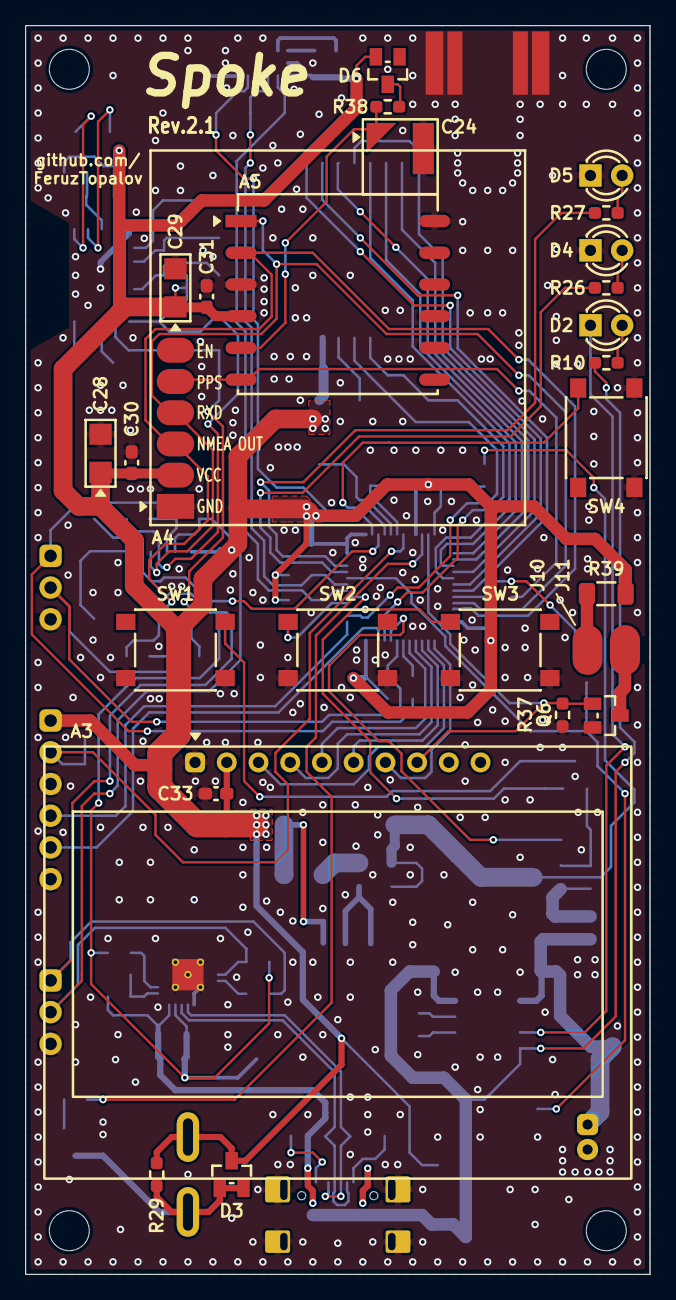
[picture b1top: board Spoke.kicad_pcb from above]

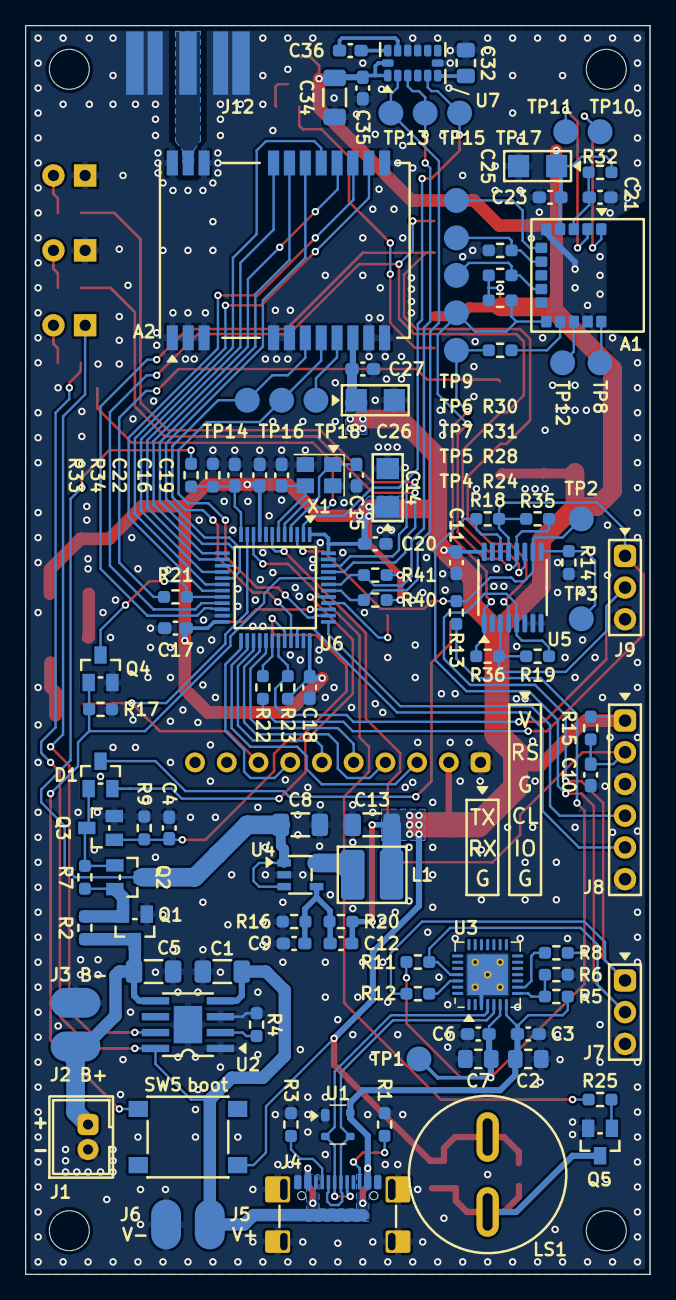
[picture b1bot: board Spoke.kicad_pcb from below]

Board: 2 copper layers, 50.0 x 100.0 mm, 143 parts (111 on the bottom side), 89 nets.

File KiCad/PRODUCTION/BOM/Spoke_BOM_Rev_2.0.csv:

#,Reference,Value,Qty,Footprint,Description
1,A1,E104-BT5005A,1,Spoke:E104-BT5005A,Ebyte BLE-UART module
2,A2,E22-400M22S,1,Spoke:E22,Ebyte LoRa module
3,A3,GM12864-01A,1,Spoke:GM12864-01A,ST7567-based monochrome LCD module
4,A4,GN-801,1,Spoke:GN-801,GPS module
5,C33,220nF,1,Spoke:C0603,Ceramic capacitor
6,"C1,C5,C8,C13,C31",10uF,5,Spoke:C1206,Ceramic capacitor
7,"C14,C24,C25,C27",47uF,4,Spoke:C_tantA,Tantalum capacitor
8,"C15,C19",12pF,2,Spoke:C0603,Ceramic capacitor
9,"C2,C7,C28",4.7uF,3,Spoke:C0805,Ceramic capacitor
10,"C3,C6,C10,C11,C16,C17,C18,C20,C21,C22,C23,C26,C29,C30,C32",100nF,15,Spoke:C0603,Ceramic capacitor
11,D1,BAT54C,1,Spoke:SOT-23,Schottky diode array
12,D4,Green,1,Spoke:LED_3mm,Through hole 3 mm LED
13,"D2,D3",Red,2,Spoke:LED_3mm,Through hole 3 mm LED
14,J1,B2B-PH-K-S,1,Spoke:B2B-PH-2.0,JST 2.0 mm connector
15,J4,GCT USB4105/USB4110,1,Spoke:USB_C_16p_GCT4105,16-pin USB-C connector
16,J8,PLS-1x6,1,Spoke:Header_1x6,Pin header 2.54 mm
17,J12,Amphenol 132289,1,Spoke:SMA,"SMA connector, board edge, 1.6 mm PCB"
18,"J7,J9",PLS-1x3,2,Spoke:Header_1x3,Pin header 2.54 mm
19,L1,2.2uH,1,Spoke:L1616,"1616 (4040 metric) wirewound inductor, 2 A"
20,LS1,Buzzer-Passive,1,Spoke:Buzzer,"Passive buzzer (no generator), 4-8 mm pitch"
21,"Q1,Q2",AO3407A,2,Spoke:SOT-23,"P-MOSFET, 30 V, 4 A"
22,"Q3,Q4",AO3400,2,Spoke:SOT-23,"N-MOSFET, 30 V, 5 A"
23,R5,22.1kR,1,Spoke:R0603,"Chip resistor, 1%"
24,R6,47.5kR,1,Spoke:R0603,"Chip resistor, 1%"
25,R20,0R,1,Spoke:R0603,Chip resistor
26,"R1,R3",5.1kR,2,Spoke:R0603,Chip resistor
27,"R4,R21,R39,R40",3.9kR,4,Spoke:R0603,Chip resistor
28,"R7,R9,R11,R13,R14,R15,R17,R23,R29,R30,R31,R32,R35,R36",100kR,14,Spoke:R0603,Chip resistor
29,"R8,R10,R12,R22,R25,R26,R27,R28",1kR,8,Spoke:R0603,Chip resistor
30,"SW1,SW2,SW3,SW4",~,4,Spoke:Button_6x6,"SPST-NO tactile switch, 6.0 x 6.0 mm"
31,U1,SP0503BAHTG,1,Spoke:SOT-143,TVS diodes array for USB protection
32,U2,TP4056,1,Spoke:SOIC-8-EP,Li-ion charger IC
33,U3,CP2102N-A02-GQFN28,1,Spoke:QFN-28,"USB-UART IC, 28 pin (!) QFN package"
34,U4,LM3671MF-3.3,1,Spoke:SOT-23-5,"DC/DC converter IC, fixed 3.3 V"
35,U5,74HC4052PW,1,Spoke:TSSOP-16,Dual 4-ch analog MUX
36,U6,STM32F103C8T6,1,Spoke:LQFP-48,MCU
37,U7,LSM303DLHC,1,Spoke:LGA-14,3-axis accelerometer + 3-axis magnetometer
38,X1,8MHz,1,Spoke:Xtal_3225,Crystal oscillator 3.2 x 2.5 mm

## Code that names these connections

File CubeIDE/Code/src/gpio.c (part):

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    //Port A
    RCC->APB2ENR |= RCC_APB2ENR_IOPAEN;
    
    //PA0 - Passive Buzzer (PWM) Positive line in Differential drive
    //PA0 - Passive Buzzer (PWM) Single line in Sidgle-ended drive
    GPIOA->CRL &= ~GPIO_CRL_MODE0_0;    //output 2 MHz
    GPIOA->CRL |= GPIO_CRL_MODE0_1;
    GPIOA->CRL &= ~GPIO_CRL_CNF0_0;       //alternate output push-pull
    GPIOA->CRL |= GPIO_CRL_CNF0_1;
    
    //PA1 - Piezo Buzzer (PWM) Negative line in Differential drive
    //PA1 - LCD Backlight (PWM) in PWM mode Backlight
    GPIOA->CRL &= ~GPIO_CRL_MODE1_0;  	//output 2 MHz
    GPIOA->CRL |= GPIO_CRL_MODE1_1;
    GPIOA->CRL &= ~GPIO_CRL_CNF1_0;    	//alternate output push-pull
    GPIOA->CRL |= GPIO_CRL_CNF1_1;
    
    //PA2 - ADC2 (Battery voltage)
    GPIOA->CRL &= ~GPIO_CRL_MODE2;      //input mode
    GPIOA->CRL &= ~GPIO_CRL_CNF2;       //analog input
    
    //PA3 - RF Reset
    GPIOA->CRL &= ~GPIO_CRL_MODE3_0;   //output 2 MHz
    GPIOA->CRL |= GPIO_CRL_MODE3_1;
    GPIOA->CRL &= ~GPIO_CRL_CNF3;      //output push-pull
    
    //PA4 - RF CS
    GPIOA->CRL &= ~GPIO_CRL_MODE4_0;   //output 2 MHz
    GPIOA->CRL |= GPIO_CRL_MODE4_1;
    GPIOA->CRL &= ~GPIO_CRL_CNF4;      //output push-pull

    //PA5 - RF SCK
    GPIOA->CRL &= ~GPIO_CRL_MODE5_0;    //output 2 MHz
    GPIOA->CRL |= GPIO_CRL_MODE5_1;
    GPIOA->CRL &= ~GPIO_CRL_CNF5_0;     //alternate output push-pull
    GPIOA->CRL |= GPIO_CRL_CNF5_1;

    //PA6 - RF MISO
    GPIOA->CRL &= ~GPIO_CRL_MODE6;      //input mode
    GPIOA->CRL |= GPIO_CRL_CNF6_0;      //floating input
    GPIOA->CRL &= ~GPIO_CRL_CNF6_1;

    //PA7 - RF MOSI
    GPIOA->CRL &= ~GPIO_CRL_MODE7_0;    //output 2 MHz
    GPIOA->CRL |= GPIO_CRL_MODE7_1;
    GPIOA->CRL &= ~GPIO_CRL_CNF7_0;     //alternate output push-pull
    GPIOA->CRL |= GPIO_CRL_CNF7_1;

    //PA8 - LCD D/C
    GPIOA->CRH &= ~GPIO_CRH_MODE8_0;   //output 2 MHz
    GPIOA->CRH |= GPIO_CRH_MODE8_1;
    GPIOA->CRH &= ~GPIO_CRH_CNF8;      //output push-pull
    
    //PA9 - USART1 TX (Console)
    GPIOA->CRH &= ~GPIO_CRH_MODE9_0;    //output 2 MHz
    GPIOA->CRH |= GPIO_CRH_MODE9_1;
    GPIOA->CRH &= ~GPIO_CRH_CNF9_0;     //alternate output push-pull
    GPIOA->CRH |= GPIO_CRH_CNF9_1;

    //PA10 - USART1 RX (Console)
    GPIOA->CRH &= ~GPIO_CRH_MODE10;     //input
    GPIOA->CRH |= GPIO_CRH_CNF10_0;     //alternate input floating
    GPIOA->CRH &= ~GPIO_CRH_CNF10_1;
    GPIOA->ODR |= GPIO_ODR_ODR10;       //pull-up for stability

    //PA11 - RF TX Enable (in HW 1.x or 2.0) or Power Switch Hold (in HW 2.1 and above)
    GPIOA->CRH &= ~GPIO_CRH_MODE11_0;   //output 2 MHz
    GPIOA->CRH |= GPIO_CRH_MODE11_1;
    GPIOA->CRH &= ~GPIO_CRH_CNF11;      //output push-pull
    
    //PA12 - RF RX Enable
    GPIOA->CRH &= ~GPIO_CRH_MODE12_0;   //output 2 MHz
    GPIOA->CRH |= GPIO_CRH_MODE12_1;
    GPIOA->CRH &= ~GPIO_CRH_CNF12;      //output push-pull
    GPIOA->ODR |= GPIO_ODR_ODR12;		//enable RX on power-up

    //PA15 - Power Switch Hold (in HW 1.x or 2.0) or RF TX Enable (in HW 2.1 and above)
    GPIOA->CRH &= ~GPIO_CRH_MODE15_0;   //output 2 MHz
    GPIOA->CRH |= GPIO_CRH_MODE15_1;
    GPIOA->CRH &= ~GPIO_CRH_CNF15;      //output push-pull
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    //Port B
    RCC->APB2ENR |= RCC_APB2ENR_IOPBEN;
    
    //PB0 - RF IRQ (rising edge)
    GPIOB->CRL &= ~GPIO_CRL_MODE0;      //input mode
    GPIOB->CRL &= ~GPIO_CRL_CNF0_0;     //input with pull
    GPIOB->CRL |= GPIO_CRL_CNF0_1;
    GPIOB->ODR &= ~GPIO_ODR_ODR0;       //pull-down
    
    //PB1 - RF Busy
    GPIOB->CRL &= ~GPIO_CRL_MODE1;      //input mode
    GPIOB->CRL &= ~GPIO_CRL_CNF1_0;     //input with pull
    GPIOB->CRL |= GPIO_CRL_CNF1_1;
    GPIOB->ODR &= ~GPIO_ODR_ODR1;       //pull-down

    //PB2 - GPS (PPS interrupt)
    GPIOB->CRL &= ~GPIO_CRL_MODE2;     //input mode
    GPIOB->CRL &= ~GPIO_CRL_CNF2_0;    //input with pull
    GPIOB->CRL |= GPIO_CRL_CNF2_1;
    GPIOB->ODR &= ~GPIO_ODR_ODR2;      //pull-down

    //PB3 - Button ESC
    GPIOB->CRL &= ~GPIO_CRL_MODE3;      //input mode
    GPIOB->CRL &= ~GPIO_CRL_CNF3_0;     //input with pull
    GPIOB->CRL |= GPIO_CRL_CNF3_1;
    GPIOB->ODR |= GPIO_ODR_ODR3;        //pull-up on

    //PB4 - Button OK
    GPIOB->CRL &= ~GPIO_CRL_MODE4;      //input mode
    GPIOB->CRL &= ~GPIO_CRL_CNF4_0;     //input with pull
    GPIOB->CRL |= GPIO_CRL_CNF4_1;
    GPIOB->ODR |= GPIO_ODR_ODR4;        //pull-up on

    //PB5 - Button PWR
    GPIOB->CRL &= ~GPIO_CRL_MODE5;      //input mode
    GPIOB->CRL &= ~GPIO_CRL_CNF5_0;     //input with pull
    GPIOB->CRL |= GPIO_CRL_CNF5_1;
    GPIOB->ODR |= GPIO_ODR_ODR5;        //pull-up on

    //PB6 - ACC/MAG SCL
    GPIOB->CRL &= ~GPIO_CRL_MODE6_0;   //output 2 MHz
    GPIOB->CRL |= GPIO_CRL_MODE6_1;
    GPIOB->CRL |= GPIO_CRL_CNF6;       //alternate function open-drain

    //PB7 - ACC/MAG SCL
    GPIOB->CRL &= ~GPIO_CRL_MODE7_0;   //output 2 MHz
    GPIOB->CRL |= GPIO_CRL_MODE7_1;
    GPIOB->CRL |= GPIO_CRL_CNF7;       //alternate function open-drain

    //PB8 - Red LED
    GPIOB->CRH &= ~GPIO_CRH_MODE8_0;    //output 2 MHz
    GPIOB->CRH |= GPIO_CRH_MODE8_1;
    GPIOB->CRH &= ~GPIO_CRH_CNF8;       //output push-pull

    //PB9 - Green LED
    GPIOB->CRH &= ~GPIO_CRH_MODE9_0;    //output 2 MHz
    GPIOB->CRH |= GPIO_CRH_MODE9_1;
    GPIOB->CRH &= ~GPIO_CRH_CNF9;       //output push-pull
    
    //PB10 - USART3 TX (GPS)
    GPIOB->CRH &= ~GPIO_CRH_MODE10_0;    //output 2 MHz
    GPIOB->CRH |= GPIO_CRH_MODE10_1;
    GPIOB->CRH &= ~GPIO_CRH_CNF10;       //output push-pull
    GPIOB->ODR |= GPIO_ODR_ODR10;		 //workaround, this sets RX pin of the GPS to high state and prevents RX frame error which takes place when this pin is low for a long time (between gpio and uart inits)

    //PB11 - USART3 RX (GPS)
    GPIOB->CRH &= ~GPIO_CRH_MODE11;      //input
    GPIOB->CRH |= GPIO_CRH_CNF11_0;      //alternate input floating
    GPIOB->CRH &= ~GPIO_CRH_CNF11_1;
    GPIOB->ODR |= GPIO_ODR_ODR11;        //pull-up for stability

    //PB12 - LCD CS
    GPIOB->CRH &= ~GPIO_CRH_MODE12_0;   //output 2 MHz
    GPIOB->CRH |= GPIO_CRH_MODE12_1;
    GPIOB->CRH &= ~GPIO_CRH_CNF12;      //output push-pull
    
    //PB13 - LCD SCK
    GPIOB->CRH &= ~GPIO_CRH_MODE13_0;   //output 2 MHz
    GPIOB->CRH |= GPIO_CRH_MODE13_1;
    GPIOB->CRH &= ~GPIO_CRH_CNF13_0;    //alternate output push-pull
    GPIOB->CRH |= GPIO_CRH_CNF13_1;
    
    //PB14 - LCD Reset
    GPIOB->CRH &= ~GPIO_CRH_MODE14_0;   //output 2 MHz
    GPIOB->CRH |= GPIO_CRH_MODE14_1;
    GPIOB->CRH &= ~GPIO_CRH_CNF14;      //output push-pull
    
    //PB15 - LCD MOSI
    GPIOB->CRH &= ~GPIO_CRH_MODE15_0;   //output 2 MHz
    GPIOB->CRH |= GPIO_CRH_MODE15_1;
    GPIOB->CRH &= ~GPIO_CRH_CNF15_0;    //alternate output push-pull
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    //Port C
    RCC->APB2ENR |= RCC_APB2ENR_IOPCEN;

    //PC13 - ACC/MAG IRQ
    GPIOC->CRH &= ~GPIO_CRH_MODE13;      //input mode
    GPIOC->CRH &= ~GPIO_CRH_CNF13_0;     //input with pull
    GPIOC->CRH |= GPIO_CRH_CNF13_1;
    GPIOC->ODR |= GPIO_ODR_ODR13;        //pull-up

    //PC14 - USB/BLE Console Multiplexer Switch
    mux_console_usb();					 //pre-set MUX state to log 1 (USB default)
    GPIOC->CRH &= ~GPIO_CRH_MODE14_0;    //output 2 MHz
    GPIOC->CRH |= GPIO_CRH_MODE14_1;
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

#ifdef SPLIT_PWM_BUZZER_BACKLIGHT
    //PC15 - Button Alarm
    GPIOC->CRH &= ~GPIO_CRH_MODE15;      //input mode
    GPIOC->CRH &= ~GPIO_CRH_CNF15_0;     //input with pull
    GPIOC->CRH |= GPIO_CRH_CNF15_1;
    GPIOC->ODR |= GPIO_ODR_ODR15;        //pull-up on
#else
    //PC15 - LCD baclkight
    GPIOC->CRH &= ~GPIO_CRH_MODE15_0;    //output 2 MHz
    GPIOC->CRH |= GPIO_CRH_MODE15_1;
    GPIOC->CRH &= ~GPIO_CRH_CNF15;       //output push-pull
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//Init external interrupts
void ext_int_init(void)
{
    //PB0 - RF IRQ
    AFIO->EXTICR[0] |= AFIO_EXTICR1_EXTI0_PB;	//exti 0 source is port B
    EXTI->RTSR |= EXTI_RTSR_TR0;				//interrupt 0 on rising edge
    EXTI->IMR |= EXTI_IMR_MR0;					//unmask interrupt 0
    NVIC_EnableIRQ(EXTI0_IRQn);             	//enable interrupt

    //PB2 - GPS PPS interrupt on rising edge
    AFIO->EXTICR[0] |= AFIO_EXTICR1_EXTI2_PB;	//exti 2 source is port B
    EXTI->RTSR |= EXTI_RTSR_TR2;				//interrupt 2 on rising edge
    EXTI->IMR |= EXTI_IMR_MR2;					//unmask interrupt 2
    NVIC_EnableIRQ(EXTI2_IRQn);             	//enable interrupt

    //PB3 - DOWN/ESC button
    AFIO->EXTICR[0] |= AFIO_EXTICR1_EXTI3_PB;	//exti 3 source is port B
    EXTI->FTSR |= EXTI_FTSR_TR3;				//interrupt 3 on falling edge
    NVIC_EnableIRQ(EXTI3_IRQn);             	//enable interrupt

    //PB4 - UP/OK button
    AFIO->EXTICR[1] |= AFIO_EXTICR2_EXTI4_PB;	//exti 4 source is port B
    EXTI->FTSR |= EXTI_FTSR_TR4;				//interrupt 4 on falling edge
    NVIC_EnableIRQ(EXTI4_IRQn);             	//enable interrupt

    //PB5 - PWR button
    AFIO->EXTICR[1] |= AFIO_EXTICR2_EXTI5_PB;   //exti 5 source is port B
    EXTI->FTSR |= EXTI_FTSR_TR5;                //interrupt 5 on falling edge
    NVIC_EnableIRQ(EXTI9_5_IRQn);               //enable interrupt

    //PC13 - ACC interrupt
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
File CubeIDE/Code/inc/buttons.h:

/*
	SPOKE
    
    file: buttons.h
*/



#ifndef BUTTONS_HEADER
#define BUTTONS_HEADER



#define BUTTON_PRESSED_COUNTER_THRESHOLD    (55)       	//short or long click boundary


//Button physical pins 		(pin number)
#define BUTTON_DOWN_ESC_PB3	(3)
#define BUTTON_UP_OK_PB4	(4)
#define BUTTON_PWR_PB5		(5)


//Button actions
#define BTN_NO_ACTION		(0)

#define BTN_DOWN			(1)     //PB3
#define BTN_ESC				(2)

#define BTN_UP				(3)     //PB4
#define BTN_OK				(4)

#define BTN_PWR				(5)     //PB5
#define BTN_PWR_LONG		(6)



uint8_t scan_button(uint8_t button);



#endif /*BUTTONS_HEADER*/
